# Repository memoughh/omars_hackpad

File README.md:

# Omar's Hackpad
A simple macropad consists of 4 switches, a rotary encoder ( with switch ), xiao rp2040, and the switches are aligned in 2x2 grid.
It uses direct pin connection.

# Dimensions
PCB Dimensions: 81.5mm x 61.00mm
Case Dimensions: 101mm x 65mm

# BOM
- 4x cherry mx 1.00u switch
- 1x seediuno xiao rp2040
- 1x rotary encoder

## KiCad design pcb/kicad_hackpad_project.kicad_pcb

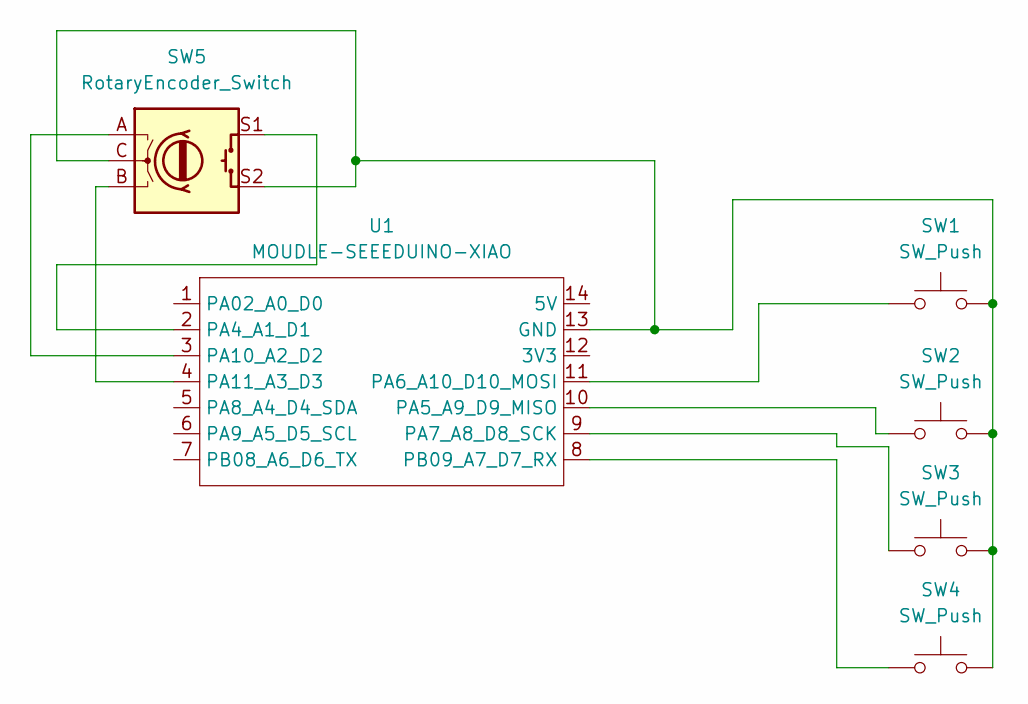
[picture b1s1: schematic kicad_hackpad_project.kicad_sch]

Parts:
SW1, SW2, SW3, SW4: SW_Push; SW_Cherry_MX_1.00u_PCB
SW5: RotaryEncoder_Switch; RotaryEncoder_Alps_EC11E-Switch_Vertical_H20mm
U1: MOUDLE-SEEEDUINO-XIAO; XIAO-Generic-Hybrid-14P-2.54-21X17.8MM

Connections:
unnamed: SW1.2, SW2.2, SW3.2, SW4.2, SW5.C, SW5.S2, U1.13 (GND)
unnamed: SW5.S1, U1.2 (PA4_A1_D1)
unnamed: SW2.1, U1.10 (PA5_A9_D9_MISO)
unnamed: SW1.1, U1.11 (PA6_A10_D10_MOSI)
unnamed: SW3.1, U1.9 (PA7_A8_D8_SCK)
unnamed: SW5.A, U1.3 (PA10_A2_D2)
unnamed: SW5.B, U1.4 (PA11_A3_D3)
unnamed: SW4.1, U1.8 (PB09_A7_D7_RX)

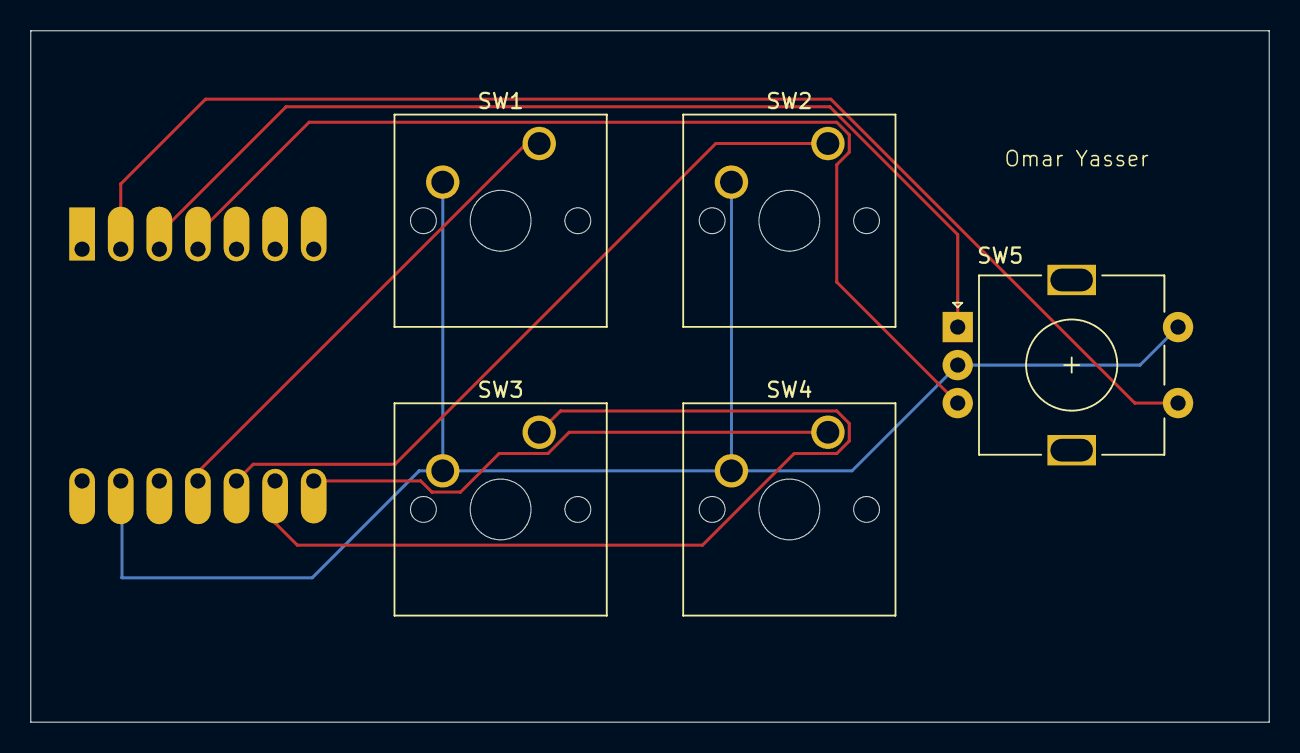
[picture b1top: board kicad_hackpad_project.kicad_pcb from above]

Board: 2 copper layers, 81.5 x 45.5 mm, 6 parts (1 on the bottom side), 8 nets.
